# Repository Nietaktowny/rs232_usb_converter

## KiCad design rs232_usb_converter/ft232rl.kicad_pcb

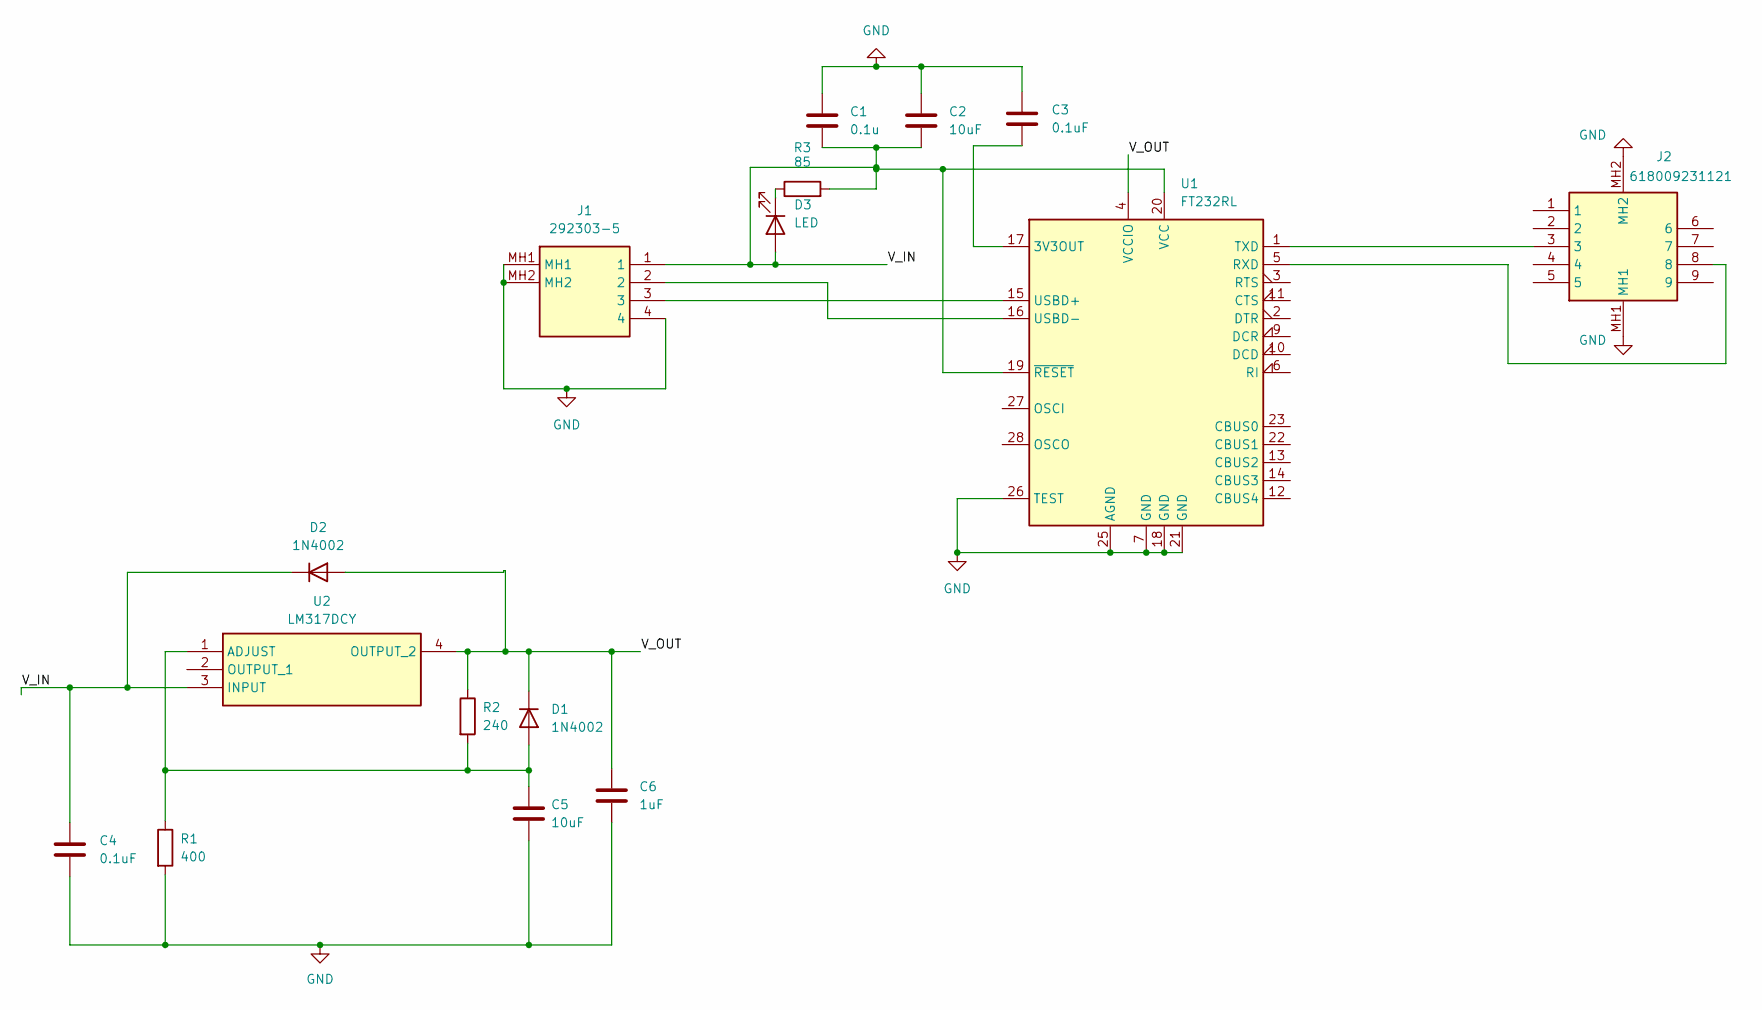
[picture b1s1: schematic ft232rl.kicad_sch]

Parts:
C1: 0.1u; C_0201_0603Metric
C2, C5: 10uF; C_0402_1005Metric
C3, C4: 0.1uF; C_0201_0603Metric
C6: 1uF; C_0201_0603Metric
D1, D2: 1N4002; D_DO-41_SOD81_P10.16mm_Horizontal
D3: LED; LED_0603_1608Metric
J1: 292303-5; 2923035; Manufacturer_Part_Number 292303-5; Mouser Part Number 571-292303-5
J2: 618009231121; Mouser Part Number 710-618009231121
R1: 400; R_1206_3216Metric
R2: 240; R_1206_3216Metric
R3: 85; R_0805_2012Metric
U1: FT232RL; SSOP-28_5.3x10.2mm_P0.65mm
U2: LM317DCY; SOT230P700X180-4N; Manufacturer_Part_Number LM317DCY; Mouser Part Number 595-LM317DCY

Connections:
/V_IN: C1.2, C2.2, C4.2, D2.1 (K), D3.2 (A), J1.1, R3.2, U1.19 (~RESET), U1.20 (VCC), U2.3 (INPUT)
/V_OUT: C6.1, D1.1 (K), D2.2 (A), R2.1, U1.4 (VCCIO), U2.4 (OUTPUT_2)
GND: C1.1, C2.1, C3.2, C4.1, C5.2, C6.2, J1.4, J1.MH1, J1.MH2, J2.MH1, J2.MH2, R1.2, U1.7 (GND), U1.18 (GND), U1.21 (GND), U1.25 (AGND), U1.26 (TEST)
unnamed: C5.1, D1.2 (A), R1.1, R2.2, U2.1 (ADJUST)
unnamed: D3.1 (K), R3.1
unnamed: C3.1, U1.17 (3V3OUT)
unnamed: J2.8, U1.5 (RXD)
unnamed: J2.3, U1.1 (TXD)
unnamed: J1.3, U1.15 (USBD+)
unnamed: J1.2, U1.16 (USBD-)

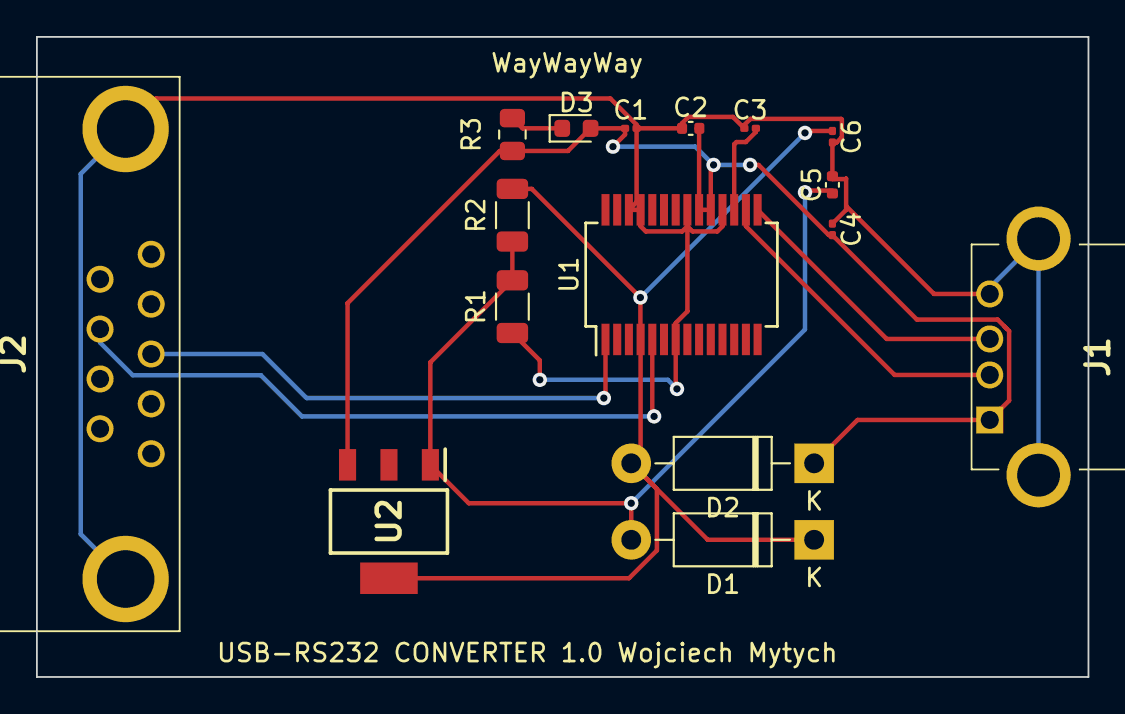
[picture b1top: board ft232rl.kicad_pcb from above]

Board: 2 copper layers, 58.4 x 35.6 mm, 16 parts (0 on the bottom side), 10 nets.

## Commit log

2023-11-13 init
